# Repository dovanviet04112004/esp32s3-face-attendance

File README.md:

# esp32s3-face-attendance

Máy chấm công nhận diện khuôn mặt chạy trọn trên một vi điều khiển ESP32-S3, và **Nhân Lực** —
hệ quản trị nhân sự nhận lượt chấm từ máy. Phát hiện mặt, chống giả mạo và nhận diện đều suy luận
ngay trên chip, ảnh không rời kiosk. Lượt chấm đi qua MQTT/TLS lên server, thành ngày công rồi
thành bảng lương. Người lao động xem công, xin nghỉ và nhận phiếu lương trên điện thoại.

Đồ án tốt nghiệp. Kiến trúc đầy đủ nằm ở [KẾ HOẠCH](docs/KE_HOACH_face_attendance_esp32s3.md);
README này là cửa vào.

## Một lượt chấm công

```
VL53L1X ─► OV5640 ─► YuNet ─► MiniFASNetV1SE ─► MobileFaceNet-ECA ─► so cosine với mẫu trên máy
có người   160×120   mặt +    thật hay giả?     vector 512-D               │
                     5 điểm                                                ▼
                                màn · loa · servo thanh chắn ◄── máy trạng thái chấm công
                                                                           │
 ┌─── ghi flash trước, gửi qua MQTT/TLS 8883 khi có mạng ──────────────────┘
 ▼
EMQX ─► NestJS API ─► PostgreSQL ─► ngày công ─► lương
        └─► dashboard Next.js và app Android, cập nhật tức thì
```

- **Mất mạng không mất công.** Kiosk ghi lượt chấm vào LittleFS trước, gửi khi có mạng. Mỗi lượt
  mang `local_id` duy nhất theo máy, server chống trùng bằng `unique(deviceId, localId)`: gửi lại
  bao nhiêu lần cũng chỉ thành một bản ghi.
- **Server giữ danh tính, máy giữ khuôn mặt** (KẾ HOẠCH §7.5). HR tạo nhân viên trên dashboard,
  khuôn mặt được chụp và ghi danh tại kiosk. Vector đặc trưng lưu trên server được mã hoá và không
  API đọc nào trả ra.
- **Kiosk tự đăng ký, server duyệt.** Máy xin vé qua HTTPS, nối broker bằng vé ấy, nhận bản cập
  nhật firmware và model qua OTA (KẾ HOẠCH §7.3, §7.7).

## Trạng thái — 02/11/2026

Chạy production từ 24/09/2026:

- Dashboard ở [app.cckiosk.io.vn](https://app.cckiosk.io.vn). Bản Android tải ở trang
  [Releases](https://github.com/dovanviet04112004/esp32s3-face-attendance/releases).
- API, broker và cơ sở dữ liệu chạy bằng Docker trên một VPS.
- Firmware 0.9.13 là bản phát hành mới nhất. Ba model chạy bằng ESP-DL trên board thật.

Số đo trên board, bộ model đang deploy, khi máy rảnh, đo 18/10
([`runtime_compare.md`](docs/measurements/runtime_compare.md)):

| | Phát hiện | Chống giả | Nhận diện | Cả ba nối nhau |
|---|---:|---:|---:|---:|
| ESP-DL, bộ đang deploy | 32,9 ms | 73,3 ms | 246,4 ms | **353,6 ms** |
| TFLite Micro + esp-nn, cùng bộ | 232,5 ms | 780,3 ms | 2.704,3 ms | 3.717,7 ms |

Cùng một bộ model thì ESP-DL nhanh hơn TFLite Micro 10,5 lần; có tải preview thì một lượt là 406,2 ms. Camera xem trước đạt 13,9 fps
([`ram.md`](docs/measurements/ram.md)), sát trần 14,2 fps của OV5640 ở XCLK 27 MHz (KẾ HOẠCH §2.1).

Độ chính xác của đúng các file đang chạy, chấm trên host bằng mô phỏng ESP-PPQ. Mô phỏng này khớp
`model->test()` trên chip:

| Nhánh | Kết quả |
|---|---|
| Phát hiện | AP 0,9544 với mặt từ 38 px, WIDER FACE val |
| Chống giả | 87 khung do chính OV5640 chụp: giữ 59/62 mặt thật, chặn 25/25 khung giả, ngưỡng 500‰ |
| Nhận diện | LFW 0,9962 · CFP-FP 0,9459 · AgeDB-30 0,9623 |

Còn mở, chi tiết ở [TASKS.md](docs/TASKS.md):

- Thời gian trọn một lượt chấm, từ lúc đứng vào tới lúc có kết quả 🔬.
- FAR/FRR trên ảnh OV5640 của nhiều người (E8-T12).
- Đáy RAM nội qua 10 phút chạy có Wi-Fi và MQTT/TLS, cần giữ từ 24 KB trở lên 🔬.
- Secure Boot và mã hoá flash chưa bật (E13-T3).
- Báo cáo ĐATN (E14): `docs/thesis/latex/` có khung và Chương 1, dựng bằng `make thesis`; các chương sau chưa viết.

## Phần cứng

| Linh kiện | Vai trò |
|---|---|
| ESP32-S3-CAM (ESP32-S3-WROOM-1 N16R8: 16 MB flash, 8 MB PSRAM octal) | xử lý, chạy cả ba model |
| OV5640 | camera DVP, khung HVGA RGB565 |
| LCD ST7796S 4,0" 320×480, cảm ứng GT911 | màn chấm công, ghi danh khuôn mặt, cài đặt |
| VL53L1X | đo khoảng cách: có người tới gần thì kiosk thức |
| MAX98357A, loa 4 Ω 3 W | âm báo |
| SG90 | servo gạt thanh chắn |
| PCF8574 | mở rộng chân: reset cảm ứng, XSHUT của VL53L1X, tắt ampli |
| DS3231 | giữ giờ khi mất mạng |

Chân GPIO khai ở đúng hai chỗ: KẾ HOẠCH §2 và
[`app_config.h`](firmware/components/bsp_board/include/app_config.h). Đổi chân thì sửa cả hai
trong cùng một commit. Sơ đồ nguyên lý và PCB (KiCad 10) sinh từ script, xem
[hardware/README.md](hardware/README.md).

## Model

| Nhánh | Kiến trúc | Đầu vào | File `.espdl` |
|---|---|---|---:|
| Phát hiện | YuNet (`yunet_n`): box và 5 điểm mốc để căn mặt | 160×120 | 193 KB |
| Chống giả | MiniFASNetV1SE, đọc vùng quanh mặt rộng 2,7 lần | 80×80 | 577 KB |
| Nhận diện | MobileFaceNet-ECA, ra vector 512-D | 112×112 | 1.346 KB |

- Lượng tử bằng ESP-PPQ theo thang bốn bậc (ADR-0006): INT8, riêng nhánh chống giả giữ một lớp
  INT16. Chạy bằng ESP-DL 3.3.11, trọng số chép sang PSRAM. TFLite Micro
  với esp-nn vẫn dựng được (`AI_RUNTIME_TFLM` trong Kconfig) để làm đối chứng.
- Model nằm ở partition riêng: hai slot `models_0` và `models_1`, mỗi slot 2,25 MB. Nhờ vậy model
  cập nhật qua OTA độc lập với firmware.
- [`contracts/models.lock.json`](contracts/models.lock.json) ghi bộ đang deploy: file, sha256, run, ngưỡng.
  Script nạp model kiểm sha256 theo lock này trước khi ghi lên board.

## Bố cục repo

| Thư mục | Nội dung |
|---|---|
| [`contracts/`](contracts/README.md) | Nguồn sự thật chung: JSON Schema của payload MQTT, danh sách topic, model đang deploy, vector vàng. `make gen` sinh DTO TypeScript và header C từ đây |
| `ml/` | Python 3.12, gói `facepipe`, quản lý bằng uv: dữ liệu, huấn luyện, lượng tử hoá, xuất và khoá model |
| `firmware/` | ESP-IDF 6.0.2, C và C++. Component chia tầng `bsp_` `drv_` `sys_` `ai_` `net_` `svc_` `ui_`, 29 test app chạy trên board |
| `hardware/` | Sơ đồ nguyên lý và PCB KiCad, sinh từ `hardware/gen/` |
| `backend/` | NestJS 12, Prisma 7, PostgreSQL 16, Redis và BullMQ, MQTT tới EMQX |
| `frontend/` | Next.js 16, React 19, Kumo; tiếng Việt và tiếng Anh; cài được như PWA |
| `android/` | Vỏ Trusted Web Activity đưa dashboard thành app Android |
| `deploy/` | Docker Compose cho máy dev và VPS, Traefik, cấu hình EMQX, sao lưu, `deploy.sh` |
| `tools/` | Sinh code và kiểm tra dùng chung: `gen_contracts`, `check_comments`, `check_layers`, `check_migrations`, `check_error_codes`, `check_schematic`, `check_pcb`… |
| `docs/` | Kế hoạch, backlog, ADR, số đo |

Ba khối `ml`, `firmware` và `backend`/`frontend` không chép định nghĩa của nhau. Payload, model
đang deploy và vector kiểm thử đều nằm ở `contracts/`, mỗi khối sinh code từ đó.

## Bắt đầu

Cần: Linux hoặc WSL2, Docker có `docker compose`, Node.js 24, Python 3.12 với
[uv](https://docs.astral.sh/uv/), và ESP-IDF v6.0.2 nếu dựng firmware. Mọi lệnh đi qua `Makefile`
ở gốc; `make help` liệt kê theo nhóm.

### Backend và dashboard

```bash
make be-install fe-install
cp deploy/.env.example deploy/.env          # điền mật khẩu
cp backend/.env.example backend/.env        # khớp mật khẩu với deploy/.env, đặt SEED_ADMIN_PASSWORD
cp frontend/.env.example frontend/.env.local
deploy/emqx/gen_certs.sh 127.0.0.1          # CA và chứng thư MQTTS; certs/ không vào git
make up                                     # EMQX, PostgreSQL, Redis, MinIO
make be-prisma be-migrate be-seed
make be-dev                                 # API ở http://localhost:3000, tài liệu API ở /docs
make fe-dev                                 # dashboard ở http://localhost:3001
```

- API nối broker bằng tài khoản dịch vụ `svc-ops`. Tạo tài khoản ấy một lần trong bảng
  `built_in_database` của EMQX, qua dashboard ở http://127.0.0.1:18083, mật khẩu là
  `EMQX_OPS_PASSWORD` (KẾ HOẠCH §7.4).
- Seed tạo `admin@kiosk.local` và một tài khoản cho mỗi vai: `hr`, `payroll`, `manager`,
  `employee`, `viewer` (`@kiosk.local`). Mọi tài khoản dùng chung mật khẩu `SEED_ADMIN_PASSWORD`.
- `make be-demo` **xoá sạch** cơ sở dữ liệu rồi nạp một công ty mẫu 5.000 người.
- `make fe-dev` chạy sau `make be-dev`, nên Next nhường cổng 3000 cho API và lấy cổng 3001.

### Firmware

```bash
. $IDF_PATH/export.sh
make fw-dev                         # profile dev: -Og, assert, console
make flash PORT=/dev/ttyACM0        # nạp rồi mở monitor
make fw-log PORT=/dev/ttyACM0       # in log của board trong 30 s
```

| Profile | Dùng cho |
|---|---|
| `dev` | gỡ lỗi: `-Og`, assert, heap poisoning, console |
| `bench` | đo: `-O2`, thống kê thời gian chạy |
| `prod` | máy thật: `-O2`, log mức WARN, không console, MQTT bắt buộc TLS |
| `fleet` | bản phát hành CI dựng từ `prod`: panic hay watchdog thì khởi động lại để rollback được |

- `prod` và `fleet` đọc thêm `firmware/sdkconfig.secrets`, file không vào git, giữ token để kiosk
  xin vé lần đầu.
- Board cắm vào Windows thì gắn sang WSL: `make usb-attach` tự tìm board `303a:1001` (cắm hai board cùng loại thì thêm `BUSID=` lấy từ `make usb-list`), rồi `make fw-mac PORT=/dev/ttyACM0` để chắc đó là board nào.
- Test app trên board: `make fw-app APP=<đường dẫn>`, rồi `make fw-app-flash APP=<đường dẫn>`.
- Đối chứng ba runtime (KẾ HOẠCH §3 lớp 5): `make fw-bench-ai RUNTIME=espdl|tflm|tflm_ansi` dựng
  `test_apps/bench_ai` vào `build_<RUNTIME>` riêng, `make fw-bench-ai-run RUNTIME=… PORT=…` nạp rồi giữ
  log cả lượt cùng cỡ ảnh, sdkconfig và phiên bản component của chính bản build đó (`make
  fw-bench-ai-facts`). `make runtime-image` đóng lock TFLM `ml/artifacts/device/locks/tflm/` từ ba run trên
  lock, `make runtime-score` chấm độ chính xác trên máy, `make runtime-check` so board với máy,
  `make runtime-report` sinh `docs/measurements/runtime_compare.md`.
- Đổi kiosk bàn giữa hai runtime trong một lệnh: `make kiosk-runtime RUNTIME=tflm|espdl PORT=/dev/ttyACM0`
  dựng bản `bench` của runtime ấy, đóng ảnh model từ lock tương ứng rồi nạp app cùng hai ngăn model một lượt.
  Đổi runtime là đổi model nhận diện: sang TFLM thì máy chưa nhận ra ai cho tới khi lấy mặt lại, về ESP-DL
  thì server gửi lại bộ mẫu cũ.

### Model

Trọng số và dataset không nằm trong repo. Đường đi của một model:

```bash
make ml-sync                     # venv của ml/; máy không có GPU thì thêm TORCH=cpu
make data-fetch data-interim data-splits
make train-det ARGS="<config>"   # tương tự train-spoof, train-recog
make quantize RUN=artifacts/<nhánh>/runs/<run>
make export BRANCH=<nhánh> MODEL=<file .espdl> RUN_ID=<nhánh>/<run> ARENA_BYTES=0
make pack PORT=/dev/ttyACM0      # đóng models.bin, kiểm sha256 theo lock, ghi cả hai slot
```

`make export` chép file vào `firmware/models/<nhánh>/` và cập nhật lock trong cùng một bước.

## Kiểm tra

```bash
make lint         # mọi kiểm tra tĩnh CI chạy: tools/ và ruff
make typecheck    # tsc của backend và frontend
make check        # sinh lại từ contracts/, fail nếu file đã commit bị lệch
make ml-test      # pytest của ml/
make be-e2e       # e2e backend như CI: Postgres, Redis, EMQX dựng riêng (SPECS= để chọn suite)
```

| Workflow | Chạy khi | Làm gì |
|---|---|---|
| `contracts` | mọi push | kiểm schema, file sinh không lệch, header biên dịch được, các `tools/check_*` |
| `ml` | đổi `ml/`, `contracts/` | ruff, pytest |
| `firmware` | đổi `firmware/`, `contracts/`, `tools/` | dựng bằng ESP-IDF 6.0.2; trên `main`, phiên bản mới thì dựng bản `fleet` và đăng lên API |
| `backend` | push ngoài `main` hay pull request đổi `backend/`, `contracts/`; `deploy` gọi lại nó | Postgres, Redis, EMQX thật: migrate, seed, typecheck, e2e, build |
| `frontend` | đổi `frontend/`, `contracts/` | typegen, tsc, build |
| `deploy` | `main` đổi `backend/`, `contracts/`, `deploy/` | test backend, đẩy image lên GHCR, SSH vào VPS chạy `deploy.sh` |

## Triển khai

Push lên `main` là deploy.

- **API.** `deploy.yml` đẩy image `ghcr.io/dovanviet04112004/cckiosk-api:<sha>`, rồi `deploy.sh`
  trên VPS kéo image, chờ `/health`. API không khoẻ trong 120 s thì tự lùi về bản trước.
- **Dashboard.** Vercel dựng `frontend/` mỗi lần push.
- **Firmware.** Tăng `PROJECT_VER` trong `firmware/CMakeLists.txt`. CI dựng bản `fleet` rồi đăng
  lên API. ADMIN mời từng máy cập nhật từ dashboard. Kiosk tải qua một link có chữ ký và hạn dùng,
  ghi vào slot đang nghỉ, và lùi bản nếu bản mới không khởi động được.
- **App Android.** `android/build.sh` dựng APK từ `twa-manifest.json`; khoá ký không nằm trong repo.
- **Sao lưu.** Mỗi đêm có bản dump, WAL thì đẩy liên tục. Tất cả được nén, mã hoá bằng age rồi
  chép ra Cloudflare R2. Sao lưu quá hạn thì API gửi thư cho ADMIN.

Lần dựng đầu trên VPS không nằm trong CD: tài khoản SSH, `.env`, chứng thư broker, tài khoản dịch
vụ EMQX và tài khoản quản trị đầu tiên đều tạo tay (KẾ HOẠCH §4.8).

## Tài liệu

| File | Nội dung |
|---|---|
| [docs/KE_HOACH_face_attendance_esp32s3.md](docs/KE_HOACH_face_attendance_esp32s3.md) | Kiến trúc, nguồn sự thật: model, phần cứng, repo, task FreeRTOS, bộ nhớ, server, hệ nhân sự |
| [docs/TASKS.md](docs/TASKS.md) | Backlog 27 epic, mã task `E<epic>-T<số>` |
| [docs/adr/](docs/adr/) | Quyết định kiến trúc, mỗi quyết định một file |
| [docs/measurements/](docs/measurements/) | Số đo trên board: latency, RAM, arena, parity, từng nhánh model |
| [docs/DPIA.md](docs/DPIA.md) | Đánh giá tác động xử lý dữ liệu cá nhân theo Điều 24 Nghị định 13/2023/NĐ-CP |
| [docs/DU_LIEU.md](docs/DU_LIEU.md) | Dataset đã tải và xử lý, số đo trên đĩa |
| [docs/FREERTOS.md](docs/FREERTOS.md) | Sổ kiểm lỗi đồng thời của firmware |
| [docs/thesis/](docs/thesis/) | Ghi chép thực nghiệm cho báo cáo |

🔬 đánh dấu số phải đo trên board thật mà chưa đo.

## Quy tắc khi sửa

- Kế hoạch đi trước code. Đổi kiến trúc thì sửa KẾ HOẠCH trước, rồi mới sửa code.
- Payload MQTT, model đang deploy và vector vàng chỉ sửa ở `contracts/`, rồi `make gen`.
- Hằng số nghiệp vụ, URL, cổng và secret có đúng một nguồn (KẾ HOẠCH §4.9), không gõ thẳng vào code.
- Không commit secret, `.env`, khoá, trọng số model, dataset hay ảnh khuôn mặt.
- Commit theo Conventional Commits, scope là đường dẫn khối: `firmware/svc_vision`,
  `backend/attendance`. Code, comment và commit viết tiếng Anh; tài liệu viết tiếng Việt.
- Trước khi đẩy: `make lint`, `make typecheck`, và test của khối đã sửa.

## License

Code trong repo theo giấy phép MIT, xem [LICENSE](LICENSE). Trọng số model và dataset không nằm
trong repo. Một phần dataset chỉ cho phép dùng cho nghiên cứu, nên bộ model hiện tại cũng chỉ dùng
cho nghiên cứu; ràng buộc của từng mắt xích ở KẾ HOẠCH §1.4.

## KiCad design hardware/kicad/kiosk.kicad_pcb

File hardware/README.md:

# `hardware/` — mạch thật mà firmware chạy trên đó

Sơ đồ nguyên lý, PCB và tài liệu linh kiện của kiosk.

**KiCad bản: 10.0.6** (`kicad-cli version`). Định dạng `.kicad_sch` đổi theo major
version và không tương thích ngược, nên bản đã ghi ở đây là bản duy nhất mở được file trong `kicad/`.
File trong `kicad/` ghi ở phiên bản định dạng `20260306` (sơ đồ) và `20260206` (PCB).

## Đọc gì trước

Trước khi mở KiCad, đọc **KẾ HOẠCH §2** — toàn bộ bảng đấu nối từng chân, chân cấm dùng, ngân
sách nguồn đều ở đó. Thư mục này không giải thích lại, nó chỉ vẽ ra.

## Cái gì vào git, cái gì không

| Thư mục | Git | Vì sao |
|---|---|---|
| `gen/` | ✅ | **Nguồn thật**: ba script sinh ra `kicad/` và `lib/` từ bảng chân §2 |
| `kicad/` | ✅ | `.kicad_sch` / `.kicad_pcb` là s-expression dạng text, diff được |
| `lib/` | ✅ | Symbol và footprint sinh từ `gen/`. Kéo về thì kèm `UPSTREAM.md` |
| `export/` | ✅ | PDF/PNG cho báo cáo, nhẹ, là thứ người chấm đọc |
| `datasheets/` | ❌ | PDF của hãng — bản quyền không thuộc dự án. Chỉ `INDEX.md` vào git |
| `vendor/` | ❌ | Sơ đồ module hãng phát hành. Chỉ `UPSTREAM.md` vào git |

`*.kicad_prl`, `*-backups/` và `fp-info-cache` là rác phiên làm việc, mỗi máy một khác — đã
gitignore.

## Sinh lại toàn bộ

Chạy từ gốc repo:

```bash
make hw-gen      # gen_fp -> lib/footprints/, gen_sch -> kicad/ + lib/symbols/, gen_pcb -> kicad/, rồi pcb upgrade và hai check
make hw-check    # ERC + DRC -> export/erc.rpt, export/drc.rpt (gitignore); lỗi hay cảnh báo nào cũng fail
make hw-export   # PDF sơ đồ mang sha7 của commit KẾ HOẠCH cuối, SVG layout, ảnh render mặt trên -> export/
```

Ba script chạy đúng thứ tự đó vì `gen_pcb` đọc sơ đồ vừa sinh để lấy net. `kicad-cli` ở máy này là
bản Windows nên chỉ nhận đường dẫn Windows; Makefile tự đổi qua `wslpath` khi `KICAD_CLI` là file `.exe`.

`pcb upgrade` là bắt buộc: `gen_pcb.py` ghi ở định dạng `20241229` rồi để KiCad nâng lên
`20260206`, vì viết thẳng định dạng mới nhất bằng tay là chép một thứ sẽ đổi ở bản sau.

**Sinh lại phải ra file y hệt.** Chạy hai lần liên tiếp mà `git status` sạch thì đúng; lệch
là có uuid nào đó đang lấy ngẫu nhiên, và mỗi lần chạy sẽ đẻ ra hai nghìn dòng diff che mất
thay đổi thật. Đừng sửa tay file trong `kicad/` — lần sinh sau mất sạch.

## Lỗ khoan

| Ø | Số lỗ | Ở đâu | Cái gì cắm vào |
|---|---|---|---|
| **0,40 mm** | 31 | rải khắp board | **Via** tín hiệu — không cắm gì, chỉ nối đồng hai mặt |
| **0,60 mm** | 15 | rải khắp board | **Via nguồn** — khoan to hơn vì mỗi cái gánh cả dòng về của một tải |
| **0,80 mm** | 10 | `R1` `C2` `C3` `C4` `C5` | Chân trở 1/4 W và chân tụ nhỏ, đều ~0,6 mm |
| **1,00 mm** | 98 | `U1` `U2` `J3` `J4` `J5` `J6` `J7` `J9` `J13` `J14`, `C1` | Chân header 2,54 mm (vuông 0,64 → chéo 0,91), chân tụ 1000 µF |
| **1,30 mm** | 4 | `J10` `J11` | Chân domino MX126-5.0 |
| **3,20 mm** | 8 | `H1`…`H4` bắt tấm màn (lỗ trên màn Ø3,5); `H5`…`H8` bắt board vào vỏ, bốn góc | Vít M3 — **không phủ đồng** (NPTH) |

**Board 2 lớp**, dày 1,6 mm. Đường nguồn 1,0 mm đi mặt sau, tín hiệu 0,25 mm đi mặt trước; đường nào
bí thì lật mặt, và chỗ lật là một via. **Mọi via đều bịt mask hai mặt trong file**, nhưng JLCPCB chỉ
bảo đảm kín tới lỗ Ø0,5, nên 15 via nguồn Ø0,6 có thể hở miệng lỗ (KẾ HOẠCH §2.5). Theo IPC-2221 ở
1 oz, dây 1,0 mm chịu **2,39 A** so với đỉnh 1,34 A của rail 1; với lớp mạ lỗ 18 µm của JLCPCB, via
Ø0,6 chịu **1,17 A** so với 0,91 A của via nặng nhất.

Vành đồng mỏng nhất **0,20 mm** (via tín hiệu); mỏng nhất trong các lỗ cắm là **0,35 mm** (các lỗ 1,00). `tools/check_pcb.py` chặn lỗ dưới 0,30 mm và
vành dưới 0,20 mm — dưới mức đó thì xưởng rẻ bắt đầu hỏi lại hoặc báo giá khác.

Bốn lỗ vít là **NPTH nên không có vành**, đó là đúng chứ không phải thiếu: có đồng quanh lỗ bắt
vít thì đầu vít chạm vào là chập. Cùng lý do, **không đồng nào trong bán kính 3,5 mm quanh cả tám
lỗ vít**, hai mặt, dây lẫn via — cỡ long đen M3. DRC chỉ đo tới mép lỗ, còn thứ đè lên mặt board
là đầu vít với trụ đồng, rộng gấp đôi lỗ (KẾ HOẠCH §2.5).

## Đặt in

`make hw-fab` xuất Gerber (đồng, mask, in lụa hai mặt, viền) và file khoan Excellon tách PTH/NPTH
vào `export/fab/` (gitignore), rồi nén thành `kiosk_<sha>.zip` để upload. Thông số chọn ở JLCPCB,
suy từ board:

| Mục | Chọn |
|---|---|
| Vật liệu, số lớp, độ dày | FR-4, 2 lớp, 1,6 mm |
| Đồng | 1 oz mặt ngoài |
| Kích thước | 158 × 121 mm, một board, không ghép tấm |
| Lỗ nhỏ nhất, dây/khe hẹp nhất | 0,40 mm; 0,25 / 0,255 mm, trong mức tiêu chuẩn |
| Via | Tented |
| In lụa | **High-precision characters**: chữ cao 0,8 mm (KẾ HOẠCH §2.3I) |
| Bề mặt | HASL |
| Lắp ráp, stencil | Không: mọi chân xuyên lỗ, hàn tay |

## Đóng KiCad trước khi sinh lại sơ đồ

KiCad giữ cả file trong bộ nhớ. Đang mở mà có ai ghi đè file dưới đĩa thì lần Save
tiếp theo của KiCad **xoá sạch** thay đổi đó — không báo gì cả. Đã mất một lần sửa
chỗ đặt linh kiện đúng theo cách này.

Hai file `~kiosk.kicad_*.lck` là dấu hiệu KiCad đang mở project; còn chúng thì không
ghi vào `kicad/`. Và mỗi lần sơ đồ đổi, chạy:

```bash
python3 tools/check_schematic.py
```

Nó đọc thẳng `kiosk.kicad_sch`, đối chiếu từng chân devkit với `app_config.h` và bắt
cả chữ chen nhau. Kiểm trên file thật nên bắt được cả thứ do KiCad ghi ra.

## §2 đúng, sơ đồ sai thì sửa sơ đồ

Chân GPIO khai ở **đúng hai chỗ**: `firmware/components/bsp_board/include/app_config.h` và KẾ
HOẠCH §2 (CLAUDE.md §1.3). Sơ đồ ở đây là **ảnh chụp** của §2, không phải nguồn thứ ba. Vẽ xong
thì đặt tên file trong `export/` kèm git sha của lần đọc §2:

```
export/kiosk_schematic_<sha7>.pdf
```

Lệch nhau thì §2 đúng và sơ đồ vẽ lại. Không bao giờ sửa §2 cho khớp bản vẽ.

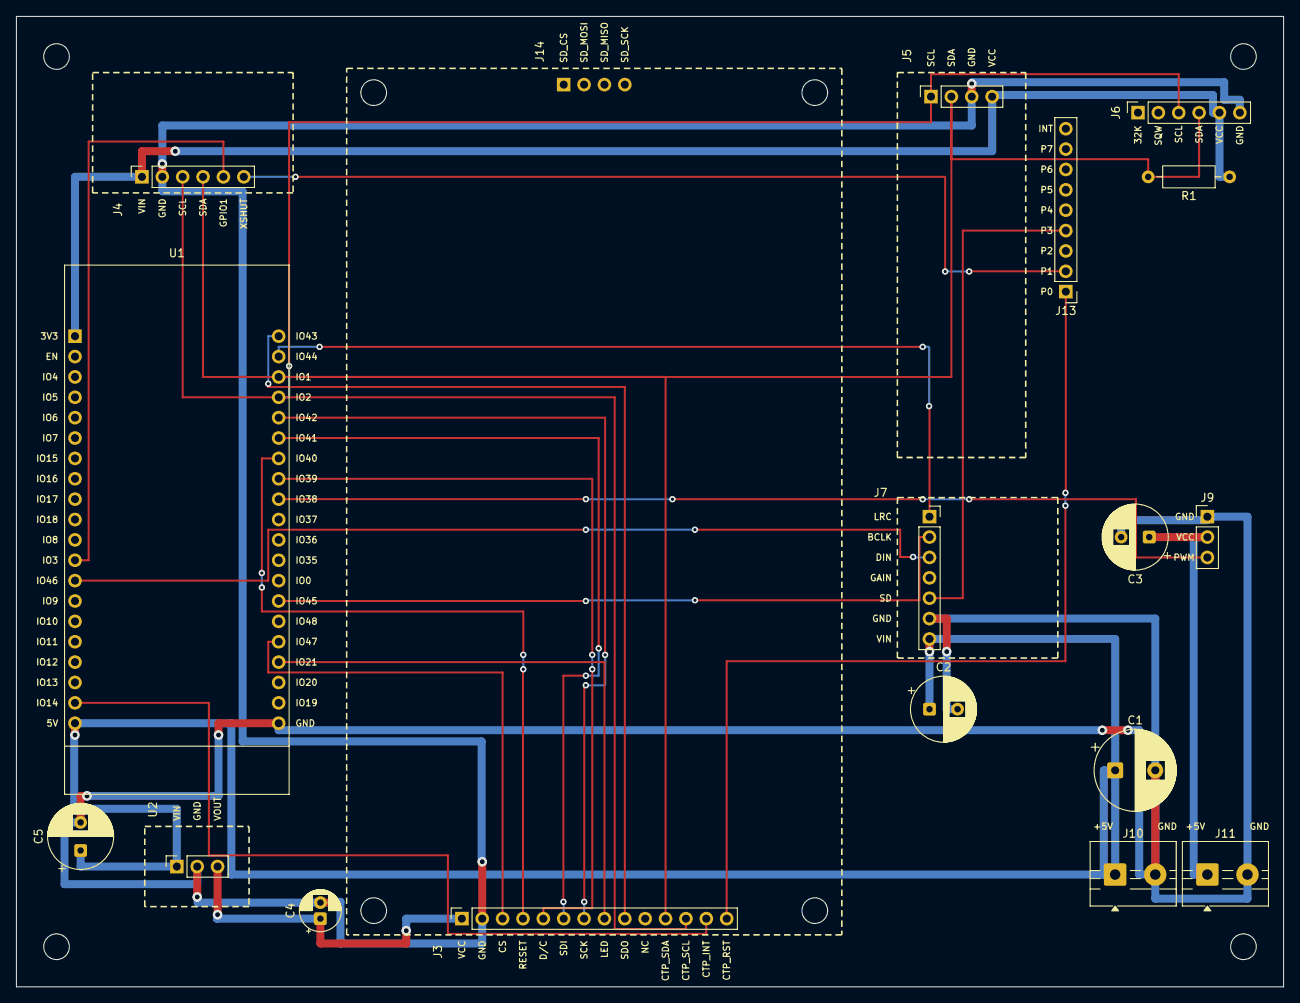
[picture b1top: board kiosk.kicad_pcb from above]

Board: 2 copper layers, 158.0 x 121.0 mm, 26 parts (0 on the bottom side), 23 nets.

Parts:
C1: CP_Radial_D10.0mm_P5.00mm
C2, C3, C5: CP_Radial_D8.0mm_P3.50mm
C4: CP_Radial_D5.0mm_P2.00mm
H1, H2, H3, H4, H5, H6, H7, H8: MountingHole_3.2mm_M3
J3: PinSocket_1x14_P2.54mm_Vertical
J4, J6: PinSocket_1x06_P2.54mm_Vertical
J5: PinSocket_1x04_P2.54mm_Vertical
J7: PinSocket_1x07_P2.54mm_Vertical
J9: PinHeader_1x03_P2.54mm_Vertical
J10, J11: TerminalBlock_MaiXu_MX126-5.0-02P_1x02_P5.00mm
J13: PinHeader_1x09_P2.54mm_Vertical
J14: BareHoles_1x04; BareHoles_1x04_P2.54mm
R1: R_Axial_DIN0207_L6.3mm_D2.5mm_P10.16mm_Horizontal
U1: ESP32-S3-CAM; ESP32-S3-CAM_2x20_P2.54mm_R25.4mm
U2: PinSocket_1x03_P2.54mm_Vertical

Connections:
+3V3: J4.1, J5.4, J6.5, R1.1, U1.1
+3V3_LCD: C4.1, J3.1, U2.3
+5V_R1: C1.1, C2.1, C5.1, J7.7, J10.1, U1.20, U2.1
+5V_R2: C3.1, J9.2, J11.1
AMP_SD: J7.5, J13.4
AUDIO_BCLK: J7.2, U1.34
AUDIO_DIN: J7.3, U1.13
AUDIO_LRC: J7.1, U1.22
GND: C1.2, C2.2, C3.2, C4.2, C5.2, J3.2, J4.2, J5.3, J6.6, J7.6, J9.1, J10.2, J11.2, U1.40, U2.2
I2C_SCL: J3.12, J4.3, J5.1, J6.3, U1.24
I2C_SDA: J3.11, J4.4, J5.2, J6.4, R1.2, U1.23
LCD_BLK: J3.8, U1.37
LCD_CS: J3.3, U1.36
LCD_DC: J3.5, U1.28
LCD_MOSI: J3.6, U1.26
LCD_RST: J3.4, U1.27
LCD_SCK: J3.7, U1.25
LCD_SDO: J3.9, U1.21
SERVO_PWM: J9.3, U1.29
TOF_INT: J4.5, U1.12
TOF_XSHUT: J4.6, J13.2
TOUCH_INT: J3.13, U1.19
TOUCH_RST: J3.14, J13.1
